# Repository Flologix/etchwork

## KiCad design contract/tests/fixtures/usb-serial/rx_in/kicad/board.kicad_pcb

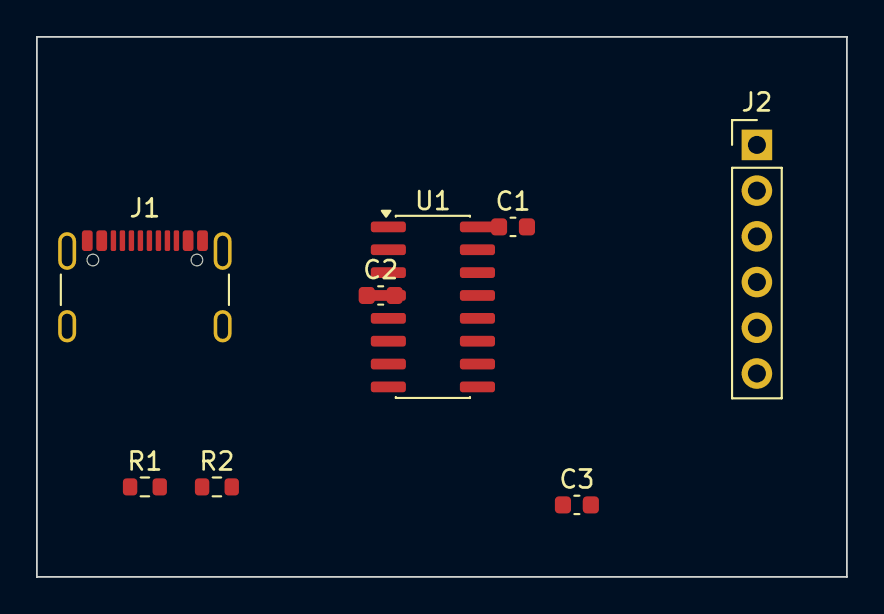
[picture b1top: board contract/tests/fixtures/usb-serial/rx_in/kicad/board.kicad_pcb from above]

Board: 2 copper layers, 45.0 x 30.0 mm, 8 parts (0 on the bottom side), 10 nets, no tracks yet.

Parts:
C1, C2, C3: 100n; C_0603_1608Metric
J1: USB_C_Receptacle_USB2.0_16P; USB_C_Receptacle_GCT_USB4105-xx-A_16P_TopMnt_Horizontal
J2: Conn_01x06; PinHeader_1x06_P2.54mm_Vertical
R1, R2: 5.1k; R_0603_1608Metric
U1: CH340C; SOIC-16_3.9x9.9mm_P1.27mm

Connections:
CC1: J1.A5 (CC1), R1.1
CC2: J1.B5 (CC2), R2.1
D+: J1.A6 (D+), J1.B6 (D+), U1.5 (UD+)
D-: J1.A7 (D-), J1.B7 (D-), U1.6 (UD-)
GND: C1.2, C2.2, J1.A1 (GND), J1.A12 (GND), J1.B1 (GND), J1.B12 (GND), J1.SH (SHIELD), J2.1, R1.2, R2.2, U1.1 (GND)
N_DTR: C3.1, U1.13 (~DTR)
N_RST: C3.2, J2.6
N_TX: J2.4, U1.2 (TXD)
N_V3: C2.1, U1.4 (V3)
VBUS: C1.1, J1.A4 (VBUS), J1.A9 (VBUS), J1.B4 (VBUS), J1.B9 (VBUS), J2.3, U1.16 (VCC)

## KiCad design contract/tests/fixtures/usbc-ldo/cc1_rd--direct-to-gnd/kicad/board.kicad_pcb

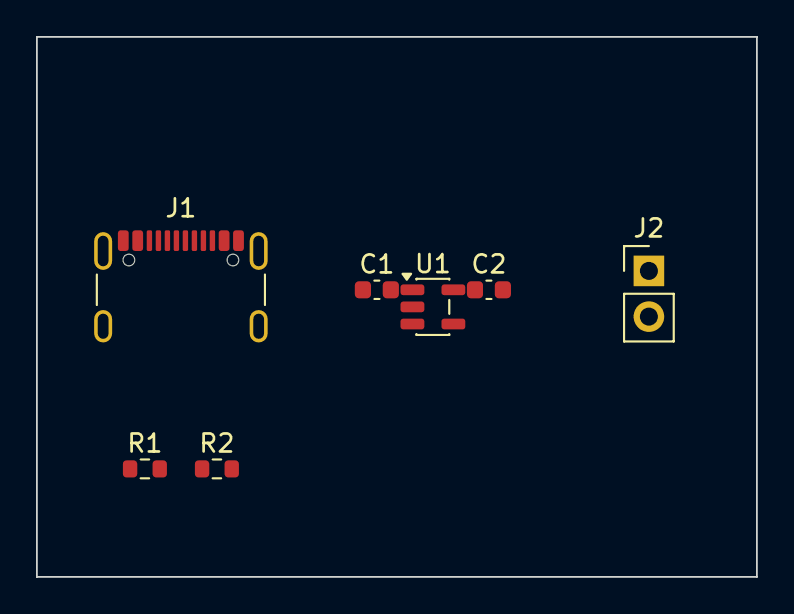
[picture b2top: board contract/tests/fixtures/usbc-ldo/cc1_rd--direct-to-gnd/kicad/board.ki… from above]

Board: 2 copper layers, 40.0 x 30.0 mm, 7 parts (0 on the bottom side), 4 nets, no tracks yet.

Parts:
C1, C2: 1u; C_0603_1608Metric
J1: USB_C_Receptacle_USB2.0_16P; USB_C_Receptacle_GCT_USB4105-xx-A_16P_TopMnt_Horizontal
J2: Conn_01x02; PinHeader_1x02_P2.54mm_Vertical
R1, R2: 5.1k; R_0603_1608Metric
U1: AP2112K-3.3; SOT-23-5

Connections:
+3V3: C2.1, J2.1, U1.5 (VOUT)
CC2: J1.B5 (CC2), R2.1
GND: C1.1, C2.2, J1.A1 (GND), J1.A5 (CC1), J1.A12 (GND), J1.B1 (GND), J1.B12 (GND), J1.SH (SHIELD), J2.2, R1.2, R2.2, U1.2 (GND)
VBUS: C1.2, J1.A4 (VBUS), J1.A9 (VBUS), J1.B4 (VBUS), J1.B9 (VBUS), U1.1 (VIN), U1.3 (EN)
